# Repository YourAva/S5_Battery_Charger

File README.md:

# S5 BATTERY CHARGER

### IMPORTANT

This project is built ontop of another individual's TP4056 board. If you wish to give your respects to the original dev, you can find their github repo that it was pulled from **[here](https://github.com/alltheworld/tp4056)**, any visits to their repo would be greatly appreciated, making sure we all work together is important! >:L

**THE FILE STRUCTURE FOR THIS PROJECT IS DOOKIE RIGHT NOW, I MIGHT FIX IT ONE DAY, BUT AS OF RIGHT NOW IT'S GONE THROUGH 8 DIFFERENT INSTALLS OF WINDOWS AND LINUX AND MULTIPLE KICAD VERSIONS BECAUSE I'M DUMB, LY!**

### Project Overview

This project was made with a pretty simple goal in mind, charging support for the S5 battery, with other options towards charging it and being able to implement it with other circuits, the project provides multiple breakout points so it can adapt to all conditions you'd ever want it to, along with the **SUPERIOR USB-C LINK!!!** ;)

## Credits -- *(thank you all :L )*
- [Original Repo](https://github.com/alltheworld/tp4056)
- [0xArya/@FairywrenTech](https://twitter.com/FairywrenTech)

## Screenshots / Renders

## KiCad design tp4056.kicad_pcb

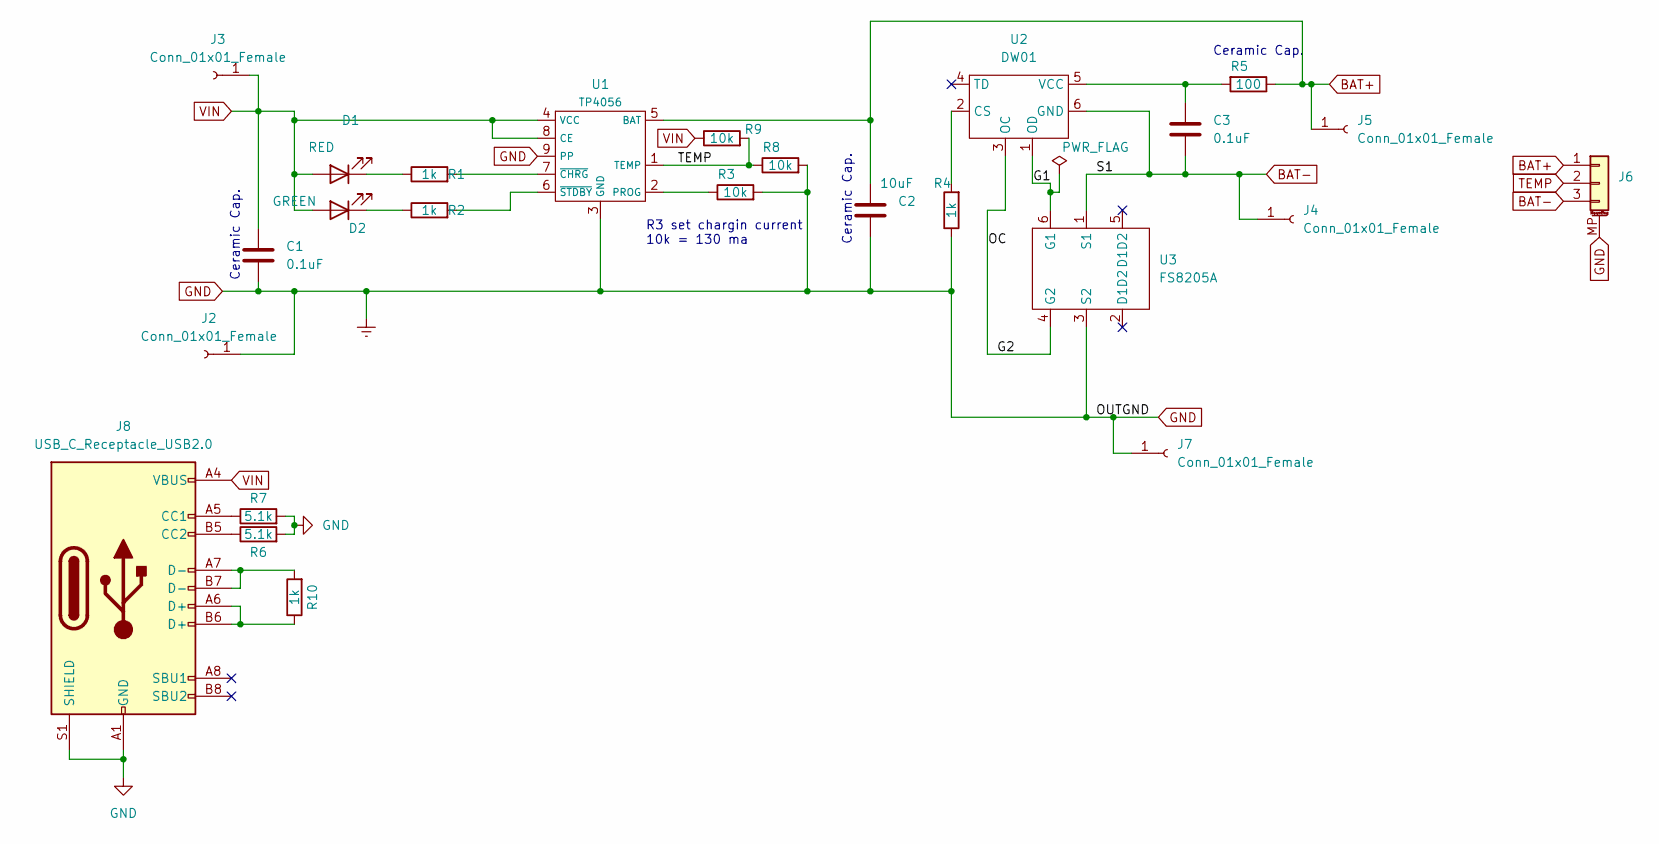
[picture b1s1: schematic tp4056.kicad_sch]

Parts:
C1, C3: 0.1uF; C_0805_2012Metric_Pad1.18x1.45mm_HandSolder
C2: 10uF; C_0805_2012Metric_Pad1.18x1.45mm_HandSolder
D1: RED; LED_0805_2012Metric_Pad1.15x1.40mm_HandSolder
D2: GREEN; LED_0805_2012Metric_Pad1.15x1.40mm_HandSolder
J2, J3, J4, J5, J7: Conn_01x01_Female; PinSocket_1x01_P2.54mm_Vertical
J6: Conn_01x03_MountingPin; CONN-SMD_BC-4-3PD
J8: USB_C_Receptacle_USB2.0; USB_C_Receptacle_HRO_TYPE-C-31-M-12
R1, R2, R4, R10: 1k; R_0603_1608Metric_Pad0.98x0.95mm_HandSolder
R3, R8, R9: 10k; R_0805_2012Metric_Pad1.20x1.40mm_HandSolder
R5: 100; R_0805_2012Metric_Pad1.20x1.40mm_HandSolder
R6, R7: 5.1k; R_0603_1608Metric_Pad0.98x0.95mm_HandSolder
U1: TP4056; SOIC-8-1EP_3.9x4.9mm_P1.27mm_EP2.29x3mm
U2: DW01; SOT-23-6_Handsoldering
U3: FS8205A; SOT-23-6_Handsoldering

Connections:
/G1: U2.1 (OD), U3.6 (G1)
/G2: U2.3 (OC), U3.4 (G2)
BAT+: C2.1, J5.1, J6.1, R5.1, U1.5 (BAT); also elsewhere on the board
BAT-: C3.2, J4.1, J6.3, U2.6 (GND), U3.1 (S1)
GND: C1.2, C2.2, J2.1, J6.MP (MountPin), J7.1, J8.A1 (GND), J8.A12 (GND), J8.B1 (GND), J8.B12 (GND), J8.S1 (SHIELD), R3.2, R4.1, R6.2, R7.2, R8.2, U1.3 (GND), U1.9 (PP), U3.3 (S2); also elsewhere on the board
unnamed: D1.1 (K), R1.1
unnamed: D2.1 (K), R2.1
unnamed: J8.A5 (CC1), R7.1
unnamed: J8.B5 (CC2), R6.1
unnamed: J8.A6 (D+), J8.B6 (D+), R10.1
unnamed: J8.A7 (D-), J8.B7 (D-), R10.2
unnamed: R3.1, U1.2 (PROG)
unnamed: R1.2, U1.7 (~CHRG)
unnamed: R2.2, U1.6 (~STDBY)
unnamed: R4.2, U2.2 (CS)
unnamed: C3.1, R5.2, U2.5 (VCC)
TEMP: J6.2, R8.1, R9.2, U1.1 (TEMP)
VIN: C1.1, D1.2 (A), D2.2 (A), J3.1, J8.A4 (VBUS), J8.A9 (VBUS), J8.B4 (VBUS), J8.B9 (VBUS), R9.1, U1.4 (VCC), U1.8 (CE); also elsewhere on the board

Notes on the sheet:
Ceramic Cap.
R3 set chargin current 10k = 130 ma

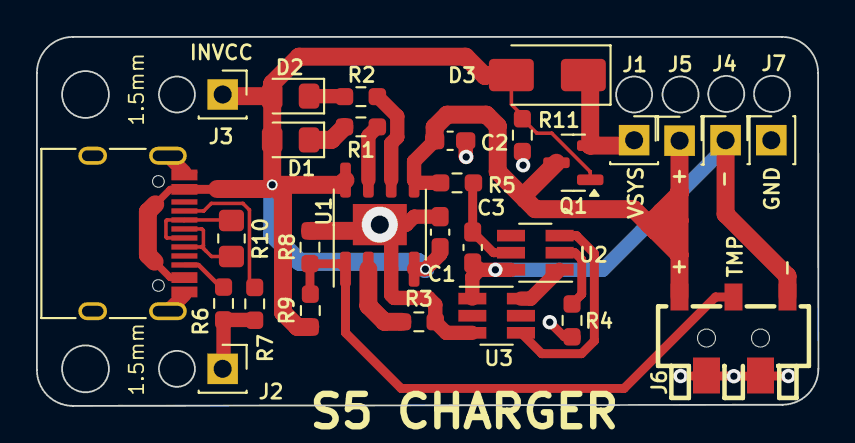
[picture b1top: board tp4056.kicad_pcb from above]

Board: 2 copper layers, 43.4 x 20.5 mm, 29 parts (0 on the bottom side), 19 nets.

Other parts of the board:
D3: SS14; D_SMA
J1: Conn_01x01_Pin; PinSocket_1x01_P2.54mm_Vertical
Q1: Q_PMOS_GSD; SOT-23
R11: 2k; R_0603_1608Metric_Pad0.98x0.95mm_HandSolder

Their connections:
/VSYS: D3.1 (K), J1.1, Q1.2 (S)
BAT+: Q1.3 (D); also elsewhere on the board
GND: R11.2; also elsewhere on the board
VIN: D3.2 (A), Q1.1 (G), R11.1; also elsewhere on the board

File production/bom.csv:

Designator,Footprint,Quantity,Value,LCSC Part #
"C1, C3",0603,2,0.1uF,
C2,0603,1,10uF,
D1,0805,1,RED,
D2,0805,1,GREEN,
J1,PinHeader_1x01_P2.54mm_Vertical,1,Conn_01x01_Pin,
"J2, J3, J4, J5, J7",PinSocket_1x01_P2.54mm_Vertical,5,Conn_01x01_Female,
J6,CONN-SMD_BC-4-3PD,1,Conn_01x03_MountingPin,
J8,USB_C_Receptacle_HRO_TYPE-C-31-M-12,1,USB_C_Receptacle_USB2.0,
"R1, R2, R4",0603,3,1k,
R10,0805,1,1k,
"R3, R8, R9",0603,3,10k,
R5,0603,1,100,
"R6, R7",0603,2,5.1k,
U1,SOIC-8-1EP_3.9x4.9mm_P1.27mm_EP2.29x3mm,1,TP4056,
U2,SOT-23-6_Handsoldering,1,DW01,
U3,SOT-23-6_Handsoldering,1,FS8205A,

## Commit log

2024-02-17 Initial Push
2024-03-08 More Additions
2024-06-30 Final Project Push
2024-07-13 adding .gitignore, yeeting some files that are uncomfy to store in git
2024-07-13 actual changes: moved components around to free some space, added power path outputting on J1, enlarged via under the package to make soldering-iron rework possible, made PROG resistor 0805; designat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
